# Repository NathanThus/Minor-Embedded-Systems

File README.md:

# Minor Embedded Systems & Signals

Welcome to my portfolio for the Fontys Minor Embedded Systems & Signals. There isn't much to look at right now, but there ought to be a bit more later.
For this semester, I'll be aiming to improve my overall skills in the embedded field, as well as learning a few things about PCB development.

## Reading Guide

**PCB** If a PCB does not fit in the context of my [personal project](Personal%20Plan.md), it can be found [here.](PCB/)

**DSP** Any assignments completed for the DSP (Digital Signal Processing) Workshops can be found [here.](DSP/)

**Certificates** Any certificates obtained go [here.](Certificates/)

**Tools** any tools I attempt to build during the course of the semester, which I believe might aid me go [here.](Tools/)

## Personal Project

[Personal Plan](/Personal%20Plan.md) - The personal project plan for this semester.

[The Making Of A Controller](./The%20Making%20Of%20A%20Controller.md) - The overall document regarding the development of my own controller.

## Passed Semester Succesfully

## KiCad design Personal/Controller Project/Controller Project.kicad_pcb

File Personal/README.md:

# Personal Folder

This is a range of products, relating to my personal project (Creating my own game controller from scratch) or any other (minor) skills and projects I took on during this semester.

[Small Project](/Personal/Small%20Project/) - Any small project will go there, in image form. These will either be breadboard projects or soldering work.

## Keysight VISACOM Project

[keysight-visa](/Personal/keysight-visa/) - A side project for reading data off an oscilloscope, via the VISA protocol. Written in C++.
[Project Documentation](./Keysight-Visa.md)

<!-- [Terrain Generation](./Terrain%20Generation/) - An attempt at mathematically approaching Terrain Generation in video games, using MATLAB to simulate a surface. -->

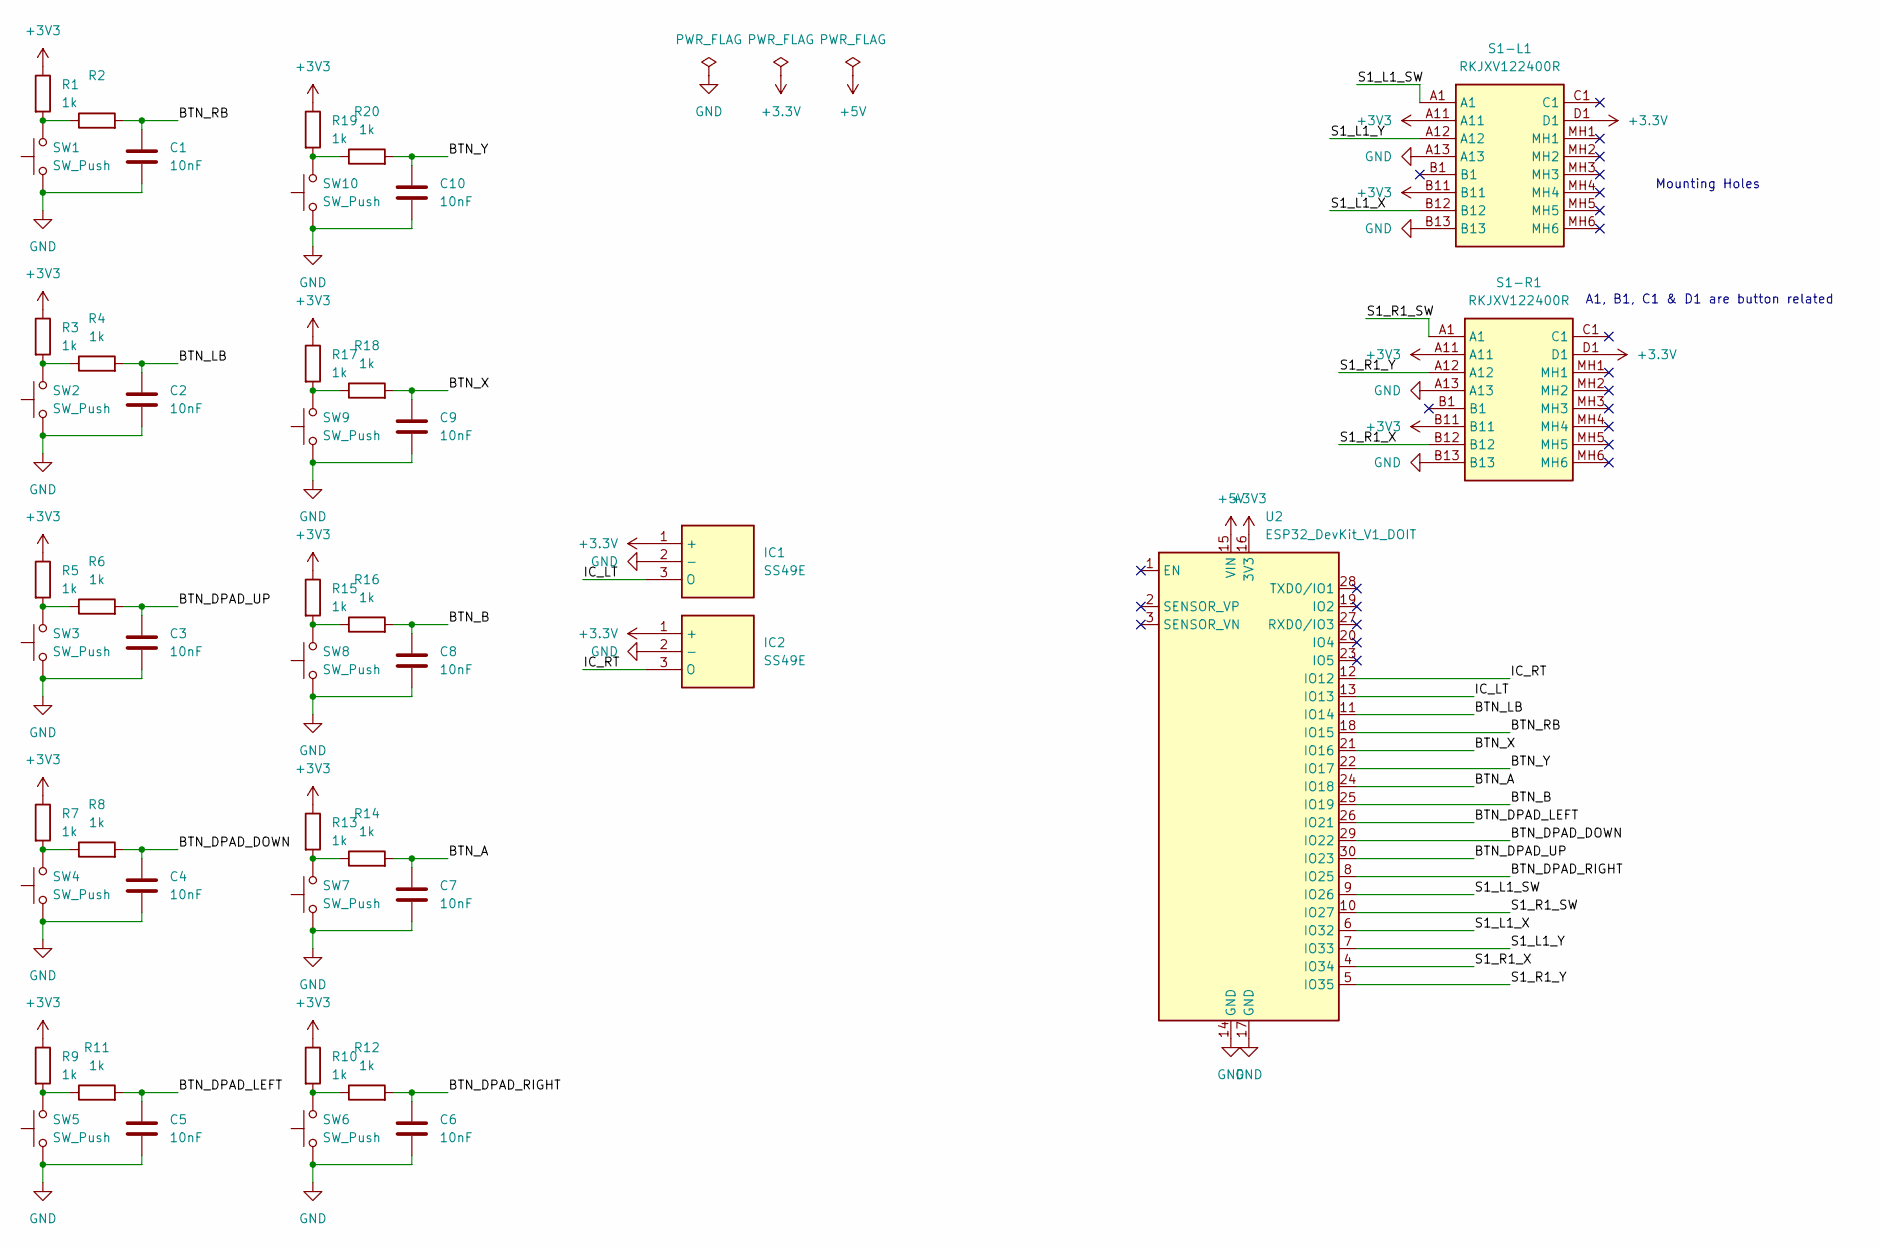
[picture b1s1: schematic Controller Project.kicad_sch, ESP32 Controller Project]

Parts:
C1, C2, C3, C4, C5, C6, C7, C8, C9, C10: 10nF; CP_Radial_D5.0mm_P2.50mm
IC1, IC2: SS49E; Mouser Part Number 785-SS49E
R1, R2, R3, R4, R5, R6, R7, R8, R9, R10, R11, R12, R13, R14, R15, R16, R17, R18, R19, R20: 1k; R_Axial_DIN0204_L3.6mm_D1.6mm_P5.08mm_Horizontal
S1-L1, S1-R1: RKJXV122400R; Mouser Part Number 688-RKJXV122400R
SW1, SW2, SW3, SW4, SW5, SW6, SW7, SW8, SW9, SW10: SW_Push; SW_PUSH_6mm
U2: ESP32_DevKit_V1_DOIT; esp32_devkit_v1_doit

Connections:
+3.3V: IC1.1 (+), IC2.1 (+), S1-L1.D1, S1-R1.D1
+3V3: R1.1, R3.1, R5.1, R7.1, R9.1, R10.1, R13.1, R15.1, R17.1, R19.1, S1-L1.A11, S1-L1.B11, S1-R1.A11, S1-R1.B11, U2.16 (3V3); also elsewhere on the board
/BTN_A: C7.1, R14.2, U2.24 (IO18); also elsewhere on the board
/BTN_B: C8.1, R16.2, U2.25 (IO19)
/BTN_DPAD_DOWN: C4.1, R8.2, U2.29 (IO22)
/BTN_DPAD_LEFT: C5.1, R11.2, U2.26 (IO21)
/BTN_DPAD_RIGHT: C6.1, R12.2, U2.8 (IO25); also elsewhere on the board
/BTN_DPAD_UP: C3.1, R6.2, U2.30 (IO23)
/BTN_LB: C2.1, R4.2, U2.11 (IO14); also elsewhere on the board
/BTN_RB: C1.1, R2.2, U2.18 (IO15); also elsewhere on the board
/BTN_X: C9.1, R18.2, U2.21 (IO16); also elsewhere on the board
/BTN_Y: C10.1, R20.2, U2.22 (IO17); also elsewhere on the board
/IC_LT: IC1.3 (O), U2.13 (IO13); also elsewhere on the board
/IC_RT: IC2.3 (O), U2.12 (IO12); also elsewhere on the board
/S1_L1_SW: S1-L1.A1, U2.9 (IO26); also elsewhere on the board
/S1_L1_X: S1-L1.B12, U2.6 (IO32); also elsewhere on the board
/S1_L1_Y: S1-L1.A12, U2.7 (IO33); also elsewhere on the board
/S1_R1_SW: S1-R1.A1, U2.10 (IO27); also elsewhere on the board
/S1_R1_X: S1-R1.B12, U2.4 (IO34); also elsewhere on the board
/S1_R1_Y: S1-R1.A12, U2.5 (IO35); also elsewhere on the board
GND: C1.2, C2.2, C3.2, C4.2, C5.2, C6.2, C7.2, C8.2, C9.2, C10.2, IC1.2 (-), IC2.2 (-), S1-L1.A13, S1-L1.B13, S1-R1.A13, S1-R1.B13, SW1.1, SW2.1, SW3.1, SW4.1, SW5.1, SW6.1, SW7.1, SW8.1, SW9.1, SW10.1, U2.14 (GND), U2.17 (GND); also elsewhere on the board
unnamed: R1.2, R2.1, SW1.2
unnamed: R3.2, R4.1, SW2.2
unnamed: R5.2, R6.1, SW3.2
unnamed: R7.2, R8.1, SW4.2
unnamed: R10.2, R12.1, SW6.2
unnamed: R9.2, R11.1, SW5.2
unnamed: R13.2, R14.1, SW7.2
unnamed: R15.2, R16.1, SW8.2
unnamed: R17.2, R18.1, SW9.2
unnamed: R19.2, R20.1, SW10.2

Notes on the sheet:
Mounting Holes
A1, B1, C1 & D1 are button related

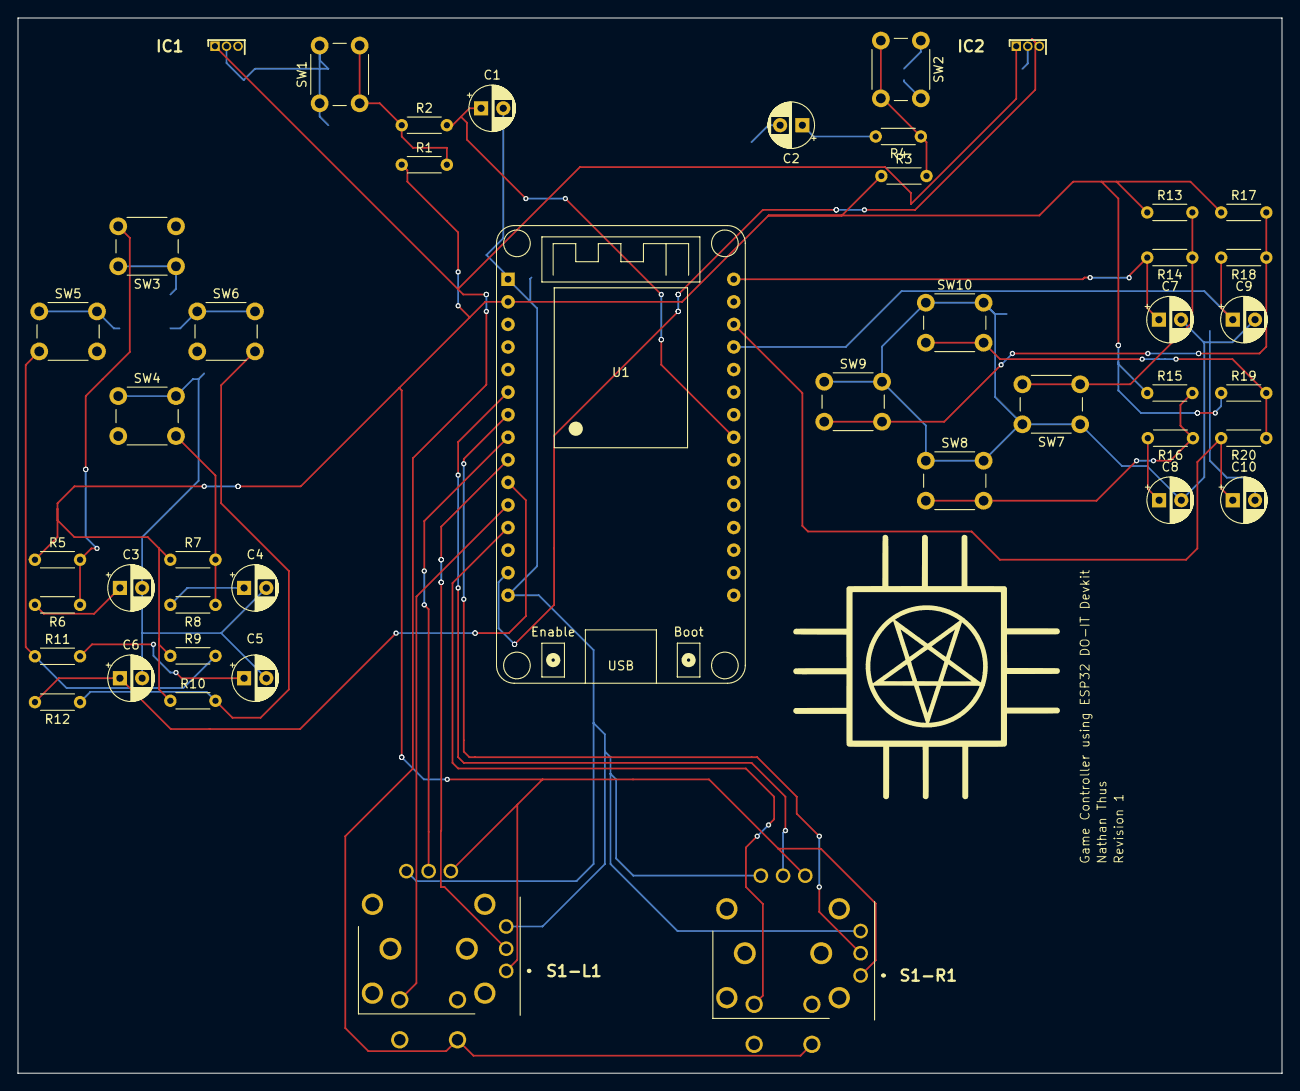
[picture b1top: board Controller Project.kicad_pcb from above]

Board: 2 copper layers, 142.2 x 118.7 mm, 45 parts (0 on the bottom side), 31 nets.

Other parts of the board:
U1: ESP32-WROOM-32; esp32_devkit_v1_doit

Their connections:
+3V3: U1.2 (VDD); also elsewhere on the board
/BTN_A: U1.30 (IO18); also elsewhere on the board
/BTN_DPAD_RIGHT: U1.10 (IO25); also elsewhere on the board
/BTN_LB: U1.13 (IO14); also elsewhere on the board
/BTN_RB: U1.23 (IO15); also elsewhere on the board
/BTN_X: U1.27 (IO16); also elsewhere on the board
/BTN_Y: U1.28 (IO17); also elsewhere on the board
/IC_LT: U1.16 (IO13); also elsewhere on the board
/IC_RT: U1.14 (IO12); also elsewhere on the board
/S1_L1_SW: U1.11 (IO26); also elsewhere on the board
/S1_L1_X: U1.8 (IO32); also elsewhere on the board
/S1_L1_Y: U1.9 (IO33); also elsewhere on the board
/S1_R1_SW: U1.12 (IO27); also elsewhere on the board
/S1_R1_X: U1.6 (IO34); also elsewhere on the board
/S1_R1_Y: U1.7 (IO35); also elsewhere on the board
GND: U1.1 (GND), U1.15 (GND); also elsewhere on the board

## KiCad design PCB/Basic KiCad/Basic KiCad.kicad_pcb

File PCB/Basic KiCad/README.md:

# Basic KiCad

This tiny project was a quick dive into KiCad, to see if designing a simple PCB is feasible within reasonable time.

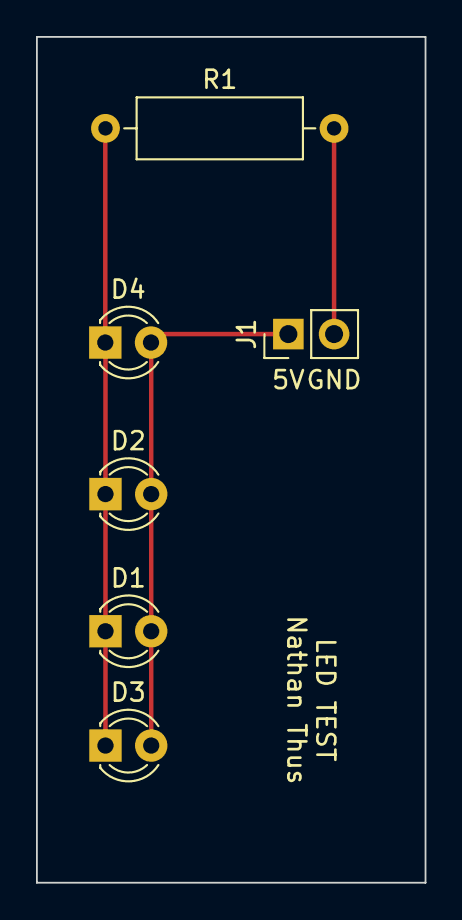
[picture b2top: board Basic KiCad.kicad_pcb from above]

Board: 2 copper layers, 21.6 x 47.0 mm, 6 parts (0 on the bottom side), 3 nets.

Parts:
D1, D2, D3, D4: LED; LED_D3.0mm
J1: PinHeader_1x02_P2.54mm_Vertical
R1: 1K; R_Axial_DIN0309_L9.0mm_D3.2mm_P12.70mm_Horizontal

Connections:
+5V: D1.2 (A), D2.2 (A), D3.2 (A), D4.2 (A), J1.1
GND: J1.2, R1.2
unnamed: D1.1 (K), D2.1 (K), D3.1 (K), D4.1 (K), R1.1

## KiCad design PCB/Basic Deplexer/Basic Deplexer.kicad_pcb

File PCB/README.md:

# PCB

- Basic KiCad
  - A simple LED circuit, for the purpose of learning about the shortcuts and design process in KiCad.
- Basic Deplexer
  - A first attempt at using IC's (Integrated Circuits) in a PCB.

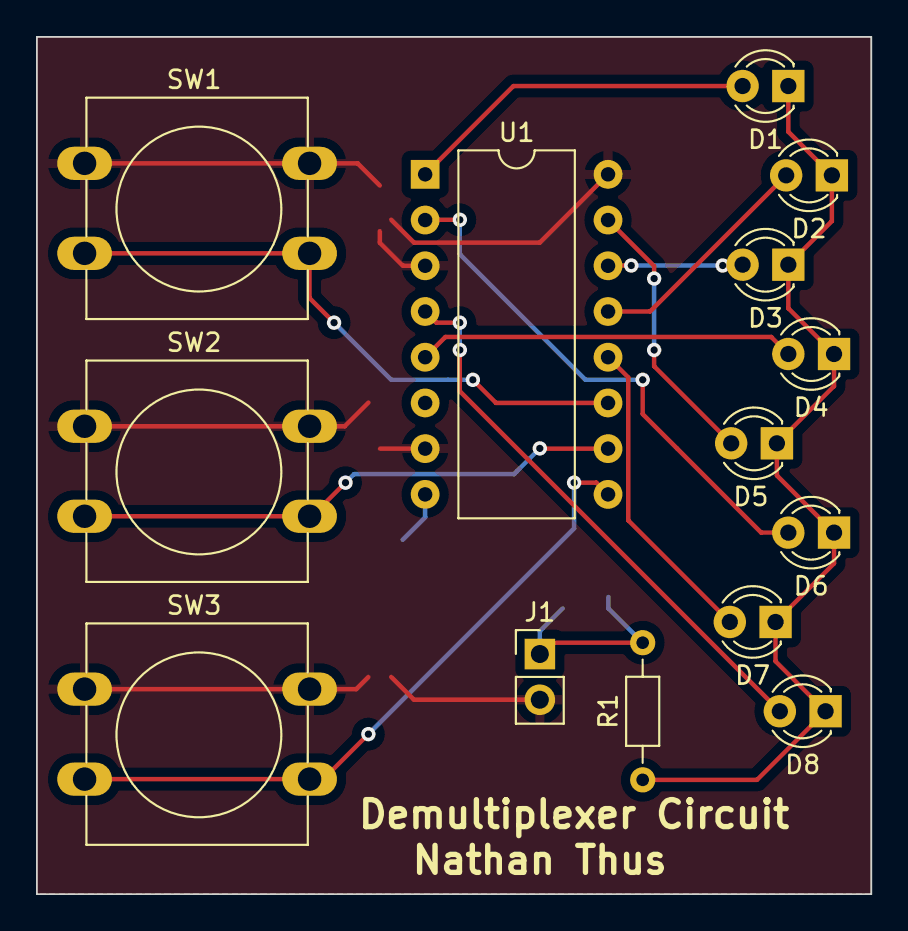
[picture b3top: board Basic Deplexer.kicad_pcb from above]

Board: 2 copper layers, 46.4 x 47.6 mm, 14 parts (0 on the bottom side), 14 nets.

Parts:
D1, D2, D3, D4, D5, D6, D7, D8: LED; LED_D3.0mm
J1: Conn_01x02_Female; PinHeader_1x02_P2.54mm_Vertical
R1: 1K; R_Axial_DIN0204_L3.6mm_D1.6mm_P7.62mm_Horizontal
SW1, SW2, SW3: SW_Push; SW_PUSH-12mm
U1: 74HC4051; DIP-16_W10.16mm

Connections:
+5V: J1.2, SW1.1, SW2.1, SW3.1, U1.3 (A), U1.7 (VEE), U1.16 (VCC)
GND: J1.1, R1.2, U1.8 (GND)
unnamed: D1.1 (K), D2.1 (K), D3.1 (K), D4.1 (K), D5.1 (K), D6.1 (K), D7.1 (K), D8.1 (K), R1.1
unnamed: D1.2 (A), U1.1 (A4)
unnamed: D2.2 (A), U1.13 (A0)
unnamed: D3.2 (A), U1.14 (A1)
unnamed: D4.2 (A), U1.5 (A5)
unnamed: D5.2 (A), U1.15 (A2)
unnamed: D6.2 (A), U1.2 (A6)
unnamed: D7.2 (A), U1.12 (A3)
unnamed: D8.2 (A), U1.4 (A7)
unnamed: SW1.2, U1.11 (S0)
unnamed: SW2.2, U1.10 (S1)
unnamed: SW3.2, U1.9 (S2)

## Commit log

2024-09-11 📝 Create basic README
2024-09-20 🙈 Update Ignore to ignore zip files
2024-09-20 🍱 Create a super simple PCB Design
2024-09-24 📝 Add Project Plan
2024-09-24 🙈 Remove .vscode references
2024-09-26 🙈 Add executables to the ignore list
2024-09-26 🎉 Finish sine wave generation project
2024-09-26 📝 Create README guide for DSP
2024-09-26 📝 Update Reading guide for DSP
2024-09-26 📝 Update documentation with spacing and execution
2024-10-04 ✨ Created a PCB with an IC
2024-10-04 🍱 Add Basic MATLAB Certification
2024-10-04 🚚 Rename parent folder for clarity
2024-10-04 📝 Updated READMEs with new information
2024-10-10 ✨ First version moving average filter MATLAB
2024-10-10 🙈 Ignore MATLAB autosave file
2024-10-10 🍱 Improve MA Filter figure clarity
2024-10-29 🚧 Work in progress tool for filter math
2024-11-01 ✨ Finalized Moving Average Filter
2024-11-01 🎉 Started Frequency Analysis
2024-11-05 🎉 Finalized Frequency Analysis
2024-11-05 ✨ Updated with the help of Gerard
    The difference in frequency was far too low, so that will be adjusted for future versions. The original concept however, was correct.
2024-11-05 🐛 Fix small naming error on the legend
2024-11-07 📝 Create Frequency Analysis Documentation
2024-11-07 📝 Update Moving Average Filter Documentation
2024-11-07 📝 Update Sine Wave Documentation
2024-11-07 📝 Update DSP reading guide
2024-11-07 📝 Update README for clarity
2024-11-08 ✨ Finalize Fourier Transform
2024-11-08 📝 Finalize documentation for Frequency Domain
2024-11-08 🎉 Start Terrain project
2024-11-20 🎉 Created Theremin
2024-11-21 📝 Update Personal Project Documentation
2024-11-29 ✨ Add reference to another repository
2024-11-29 📝 Update README for VISA project
2024-12-10 📝 Update Small project documentation
2024-12-10 📝 Update VISACOM project documentation
2024-12-10 📝 Fix linking issue to image and data
2024-12-10 📝 Create local copy of data for portfolio
2024-12-10 🎉 Start PCB Design
2024-12-10 ✨ Add Joystick to schematic
2024-12-11 🎉 Obtained the MATLAB Simulink Onramp Certificate
2024-12-11 📝 Update Certificate List
2024-12-12 🍱 Add Joystick & HAL Measurements
2024-12-12 🩹 Fix spelling mistake
2024-12-12 🩹 Fix spacing issue
2024-12-12 🩹 Fix Spacing Issues
2024-12-12 📝 Add section about hardware
2024-12-12 📝 Add section about triggers
2024-12-12 🩹 Fix minor mistake
2024-12-12 📝 Add Measurements to document
2024-12-13 🐛 Fix wrong image being output from data
2024-12-13 📝 Update documentation with VISA section
2024-12-13 📝 Add description surrounding Joystick
2024-12-19 ✨ Create VoltageDropper tool
2024-12-19 ✨ Measure HAL Sensor
    Turns out, I bought the wrong one! 😥
2024-12-19 ✨ Update schematic with new debouncing design
2024-12-19 📝 Fix typo related to data
2024-12-19 🍱 Add Debounce circuit as tested in falstad
2024-12-19 🍱 Add SS49E HAL sensor data
2024-12-19 🍱 Add bebounced button data
2024-12-19 📝 Add Documentation surrounding debounced buttons
2024-12-19 📝 Add HAL effect text
2024-12-19 📝 Fix grammatical error
2024-12-19 📝 Start writing the PCB section
2024-12-20 📝 Add Christmas Tree Solder Project to portfolio
2024-12-20 📝 Add Sources to documentation
2024-12-20 🍱 Update schematic with most of the parts
2024-12-20 📝 Add schematic to main document
2025-01-01 🍱 Update schematic with final parts
2025-01-10 🍱 Add KiCad Schematic to documentation
2025-01-10 🍱 Update Trace Design for PCB
2025-01-17 📝 Add the last documentation regarding the project
2025-01-17 🔒️ Remove Lock
2025-01-17 🍱 Update SS49E Measurements with distance data
